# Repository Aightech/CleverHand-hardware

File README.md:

# CleverHand — Hardware

This repository contains the **hardware implementation** of the CleverHand platform.

CleverHand is an open-source, modular **Human–Machine Interface (HMI) platform** designed for
research, education, and rapid prototyping in neurotechnology, robotics, and human–robot interaction.

The hardware repository provides:

* modular PCB designs (KiCad),
* mechanical integration assets,
* manufacturing outputs,
* and per-module documentation and quality metadata.

> This repository focuses **only on hardware**.
> Firmware, software, tools, and platform-level documentation live in sibling repositories.

---

## Position in the CleverHand platform

CleverHand is structured as a **hardware / firmware / software stack**:

* **Hardware** (this repo)
  Modular, chainable PCBs for sensing, actuation, and interfacing with the human body.

* **Firmware**
  Low-level drivers, bus control, synchronization, and data transport.

* **Software & SDKs**
  Host interfaces (GUI, Python, C++, LSL, ROS, etc.).

This separation allows:

* independent evolution of hardware and software,
* reproducible research setups,
* and multiple integration paths (DIY, PCBA, pre-assembled).

---

## Intended use & scope

CleverHand hardware is designed for:

* research experiments,
* educational use,
* prototyping of assistive and interactive systems.

It is **not**:

* a medical device,
* a certified clinical system,
* a consumer product.

All designs are provided **as-is**, with readiness and quality explicitly documented per module.

---

## Design goals & constraints

| Constraint          | Status | Notes                        |
| ------------------- | :----: | ---------------------------- |
| Wearable            |   ⚒️   | Wireless support in progress |
| ≥16 channels        |    ✅   | Up to 256 channels (32 × 8)  |
| ≥2 kHz bandwidth    |    ✅   | Up to 2.5 kHz                |
| ≥16-bit resolution  |    ✅   | Up to 24-bit                 |
| Bipolar / monopolar |    ✅   | Module-dependent             |
| Modular             |    ✅   | 1–32 modules per bus         |
| Affordable          |    ✅   | ~£10–£30 per module          |
| Open-source         |    ✅   | Hardware, firmware, software |

---

## Hardware architecture overview

The hardware platform is built around a **chainable modular architecture**.

Each CleverHand system is composed of:

* a **controller** (host interface and timing),
* one **communication module** (bus arbitration),
* one or more **HMI modules**, assembled from submodules.

### Submodule types

HMI nodes are built by stacking standardized submodules:

* **Communication submodule**
  Address decoding, bus routing, chip-select handling.

* **Sensor submodule**
  Biosignal or motion acquisition (EMG, IMU, etc.).

* **Feedback submodule**
  User feedback (vibration, electrotactile stimulation, LEDs).

* **Interface submodule**
  Physical interface to the body (dry electrodes, jack, flex PCB).

This structure allows:

* rapid reconfiguration,
* high channel density,
* reuse of validated building blocks.

---

## Module catalog (hardware)

> The table below lists **implemented hardware designs**.
> Readiness (prototype / reference) and quality status are tracked via
> `description.yaml`, QC artifacts, and the generated catalog — not inferred from this table.

| Module                  | Description                            | Image                                                                      | Documentation                                            |
| ----------------------- | -------------------------------------- | -------------------------------------------------------------------------- | -------------------------------------------------------- |
| Communication (COM_MOD) | Bus communication and address decoding |                     | [README](pcb/hmi/communication/COM_MOD/README.md)            |
| EMG ADS1293             | 5-channel EMG acquisition              |  | [README](pcb/hmi/submodule/sensor/EMG_DAQ_ADS1293/README.md) |
| EMG ADS1298             | 8-channel EMG acquisition              |  | [README](pcb/hmi/submodule/sensor/EMG_DAQ_ADS1298/README.md) |
| EMG INA331              | Single-channel EMG + IMU               |            | [README](pcb/hmi/submodule/sensor/EMG_INA331/README.md)      |
| FES AO4882              | Electrotactile stimulation             |          | [README](pcb/hmi/submodule/feedback/FES_AO4882/README.md)    |
| IMU ICM-20948           | 9-axis IMU                             |        | [README](pcb/hmi/submodule/sensor/IMU_ICM20948/README.md)    |
| Dry electrodes (16ch)   | Rigid dry electrode interface          |             | [README](pcb/hmi/interface/DRY_ELEC_16CH/README.md)          |

---

## Bus architecture

CleverHand uses a **shared bus architecture** combining:

* a 5-bit address bus,
* SPI for high-rate data transfer,
* I²C for identification and configuration.

Each communication module:

* monitors the address bus,
* activates the chip-select of the targeted submodule,
* routes SPI transactions accordingly.

The full line list, connector pinout, enumeration protocol and the planned v3
changes (separable bus board, per-node I²C bridge) are specified in
**[docs/bus/README.md](docs/bus/README.md)**; the 3×10 soldered stack field that
links bus board, controller/communication module and submodules inside a node is
in **[docs/bus/interfaces.md](docs/bus/interfaces.md)**.

---

## Addressing & initialization

Module addressing is determined during an initialization phase based on
**physical position in the chain**.

Modules carry no hard-coded identity: the *n*-th node in the chain receives
address *n*, so identical modules can be placed anywhere.

Current status:

* deterministic, position-based addressing: **implemented** ([protocol](docs/bus/README.md#4-enumeration-position-based-addressing))
* re-enumeration without power cycle: **planned** (v3)
* dynamic hot-plugging: **not supported**

---

## Evaluation, QC & readiness

Hardware quality and maturity are **explicitly tracked**, not implied.

For each module:

* readiness level is declared in `description.yaml`,
* QC profiles and reports live in the module’s `qc/` folder,
* catalog readiness is generated automatically.

Only **REFERENCE-level modules** are considered stable and suitable
for external reuse without direct support.

---

## Repository structure

This repository contains the hardware designs and supporting assets for the CleverHand platform.

```
├── docs
│   ├── bus             # bus & protocol specification
│   ├── datasheet
│   ├── img
│   ├── initialisation
│   └── plots
├── LICENSE
├── pcb
│   ├── config_file
│   ├── controller
│   ├── hmi
│   └── tool
├── README.md
└── scripts
```

Each top-level directory has a clear, non-overlapping responsibility, described below.

---

## Relation to other repositories

* Firmware: see top-level CleverHand firmware repository
* Software / SDKs: see CleverHand interface repository
* Platform roadmap and policies: see top-level CleverHand README

---

## Status

The CleverHand hardware platform is **actively evolving**.

Some modules are experimental; others are approaching reference quality.
Authoritative status is always given by:

* module metadata,
* QC artifacts,
* and the generated catalog.

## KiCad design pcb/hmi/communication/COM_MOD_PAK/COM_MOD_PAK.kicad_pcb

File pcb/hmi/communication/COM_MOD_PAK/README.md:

# COM_MOD_PAK — v3 communication module, version B (HC32L110 + SLG46826)

> **Status:** KiCad project created with a generated draft schematic (all parts placed with values and nets attached by labels, no wiring tidy-up, empty PCB). Generator: `scripts/boards.py`. Plots below appear after running the jobset.

Master of a chain node. Keeps the HC32L110 and its v2 enumeration firmware;
the 74HC688 comparator is replaced by an SLG46826 GreenPAK whose LUTs are
written at runtime over a **private** 2-wire link from two of the freed GPIOs.
Carries the 3×10 stack field (see
[`docs/bus/interfaces.md`](../../../../docs/bus/interfaces.md)).

## Function

```mermaid
flowchart LR
    A[A0…A4] --> PAK[SLG46826\nLUT compare, async] --> CSB
    STOPI[STOP_IN] --> FW[HC32L110\ncount / latch n] --> STOPO[STOP_OUT]
    FW -->|private I²C: LUT config| PAK
    FW -->|client 0x08+n| I2C[hardware I²C client]
    SDA[SDA / SCL] --- I2C
    SDA --> BR[PCA9306\nEN = ¬CSB] --> SDAL[SDA_L / SCL_L]
    CSB --> INV[74LVC1G04] --> BR
```

- **Enumeration**: v2 firmware untouched except `set_address()`, which writes
  the PAK LUTs instead of five GPIOs. Pin map: SDA P35, SCL P36, STOP_IN P31,
  STOP_OUT P02, LED P01, PAK link P34/P33, AUX4 P03, AUX5 P15, AUX6 P14,
  AUX7 P32, user button P23, SWDIO P27, reset P00.
- **Decode**: 4-bit LUT one-hot on `A0…A3`, 2-bit LUT on `A4`, 3-bit LUT AND +
  invert. Blank / pre-init pattern decodes "never match". No oscillator, no
  DFF; quiescent < 1 µA.
- **Private link**: bit-banged I²C on two GPIOs to the PAK only, so the shared
  bus never sees the PAK and every PAK keeps its factory address.
- **I²C bridge, STOP, LED, re-enumeration**: as `COM_MOD_PIC`.

## Stack field (3×10, all PTH)

Same pin usage as `COM_MOD_PIC`; `AUX4`…`AUX7` on HC32L110 GPIOs P03/P15/P14/P32.

## Key parts

| Function | Part | Package |
| --- | --- | --- |
| MCU | HC32L110C6UA (as `COM_MOD`; the CSP-16 variant is not routable with JLC rules) | QFN-20 3×3 0.4 mm |
| Address decoder | SLG46826V | STQFN-20 2×3 0.4 mm |
| I²C bridge | PCA9306DQER | X2SON-8 1.4×0.8 |
| CSB inverter | SN74LVC1G04DPWR | X2SON-4 0.8×0.8 |
| LED | WS2812C-2020-V1 | 2.0×2.0 |
| Button | TS-1088R-02026 | SMD |
| Programming | SWD: SWDIO, SWCLK, reset pads | — |

Decoupling 100 nF + 1 µF 0402 per IC; pull-ups as for version A; 4.7 kΩ on the
private link.

## Bench before layout

- Decode propagation at 3.3 V on a GreenPAK dev board.
- LCSC / JLC stock of SLG46826V before committing to assembly.

## Electrical schematic

## PCB layout
| top | bottom |
| --- | --- |
|  |  |

## 3D model
[COM_MOD_PAK_3D](plots/COM_MOD_PAK_pcb.stl)

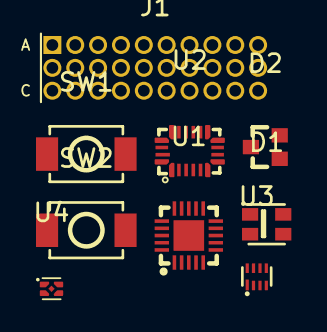
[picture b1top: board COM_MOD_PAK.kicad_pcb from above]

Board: 4 copper layers, 9 parts (0 on the bottom side), 25 nets, no tracks yet.

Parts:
D1: WS2812C-2020-V1; LED-SMD_4P-L2.0-W2.0-TL_WS2812B-2020
D2: BAT54SWT1G; SOT-323_L2.0-W1.3-P1.30-LS2.1-BR
J1: STACK 3x10; CLVHD_STACK_3x10
SW1, SW2: TS-1088R-02026; SW-SMD_L3.9-W3.0-P4.45
U1: HC32L110C6UA-SFN20TR; WQFN-20_L3.0-W3.0-P0.40-BL-EP
U2: SLG46826V_C5334557; STQFN-20_L3.0-W2.0-P0.40-BL
U3: PCA9306DQER; X2SON-8_L1.4-W1.0-P0.35-BL
U4: SN74LVC1G04DPWR; X2SON-4_L0.8-W0.8-P0.48-TL-A-1

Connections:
+3.3V: D1.4 (VDD), J1.4 (A2_3V3), U1.6 (VDD), U2.1 (VDD), U2.14 (VDD2), U3.2 (VREF1), U4.5 (VCC)
/BR_EN: U3.8 (EN), U4.4 (Y)
/BTN: SW2.1, U1.10 (LVDIN2/VCIN0/P23)
/LED_DI: D1.3 (DI), U1.2 (XTHI/AIN7/VCIN7/P01)
/PAK_SCL: U1.18 (P34/AIN4/VCIN4), U2.8 (SCL)
/PAK_SDA: U1.17 (P33/AIN3/VCIN3), U2.9 (SDA)
/RESETB: SW1.1, U1.1 (RESETB/P00)
A0: J1.2 (B1_A0), U2.2 (IO0)
A1: J1.5 (B2_A1), U2.3 (IO1)
A2: J1.8 (B3_A2), U2.4 (IO2)
A3: J1.11 (B4_A3), U2.5 (IO3)
A4: J1.14 (B5_A4), U2.6 (IO4)
AUX0: D2.1 (A), J1.9 (C3_AUX0)
AUX4: D2.3 (C/A), J1.21 (C7_AUX4), U1.7 (LVDIN1/P03)
AUX5: J1.24 (C8_AUX5), U1.8 (XTLO/P15)
AUX6: J1.27 (C9_AUX6), U1.9 (XTLI/P14)
AUX7: J1.30 (C10_AUX7), U1.16 (P32/AIN2/VCIN2)
CSB: J1.22 (A8_CSB), U2.7 (IO5), U4.2 (A)
GND: D1.2 (GND), J1.1 (A1_GND), J1.7 (A3_GND), J1.29 (B10_GND), SW1.2, SW2.2, U1.4 (VSS), U1.21 (PAD), U2.11 (GND), U3.1 (GND), U4.3 (GND)
SCL: J1.20 (B7_SCL), U1.20 (P36/AIN6/VCIN6/AVREF), U3.3 (SCL1)
SCL_L: J1.6 (C2_SCL_L), U3.6 (SCL2)
SDA: J1.17 (B6_SDA), U1.19 (P35/AIN5/VCIN5), U3.4 (SDA1)
SDA_L: J1.3 (C1_SDA_L), U3.5 (SDA2)
STOP_IN: J1.23 (B8_STOP_IN), U1.15 (P31/SWCLK)
STOP_OUT: J1.26 (B9_STOP_OUT), U1.3 (XTHO/AIN8/P02)

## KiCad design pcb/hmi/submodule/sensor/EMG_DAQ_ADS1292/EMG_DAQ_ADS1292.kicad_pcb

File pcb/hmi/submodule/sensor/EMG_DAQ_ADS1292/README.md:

# EMG ADS1292 Module
This module is a data acquisition module that embeds the ADS1292 analog front-end. It is responsible for acquiring the EMG signals from the electrodes.

## Electrical Schematic

## PCB Layout
|top view|side view|
|---|---|
 |  |  |

## 3D Model
[EMG_DAQ_ADS1292_3D](plots/EMG_DAQ_ADS1292_pcb.stl)

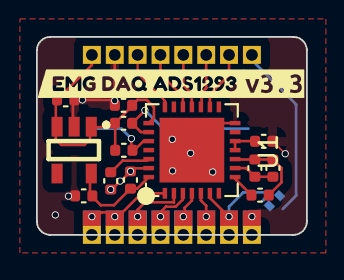
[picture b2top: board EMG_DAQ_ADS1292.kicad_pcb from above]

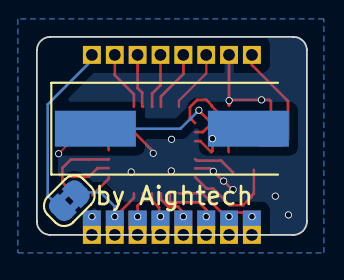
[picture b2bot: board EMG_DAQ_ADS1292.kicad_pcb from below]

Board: 4 copper layers, 15.0 x 11.0 mm, 33 parts (2 on the bottom side), 22 nets.

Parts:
C1, C5, C7: 100nF; C_0402_1005Metric
C2, C8, C9: 1uF; C_0402_1005Metric
C3, C4: 22pF; C_0402_1005Metric
C6: 1nF; C_0402_1005Metric
J1, J2, J3, J4, J5, J6, J7, J8, J9, J10, J11, J12, J13, J14, J15, J16: Conn_01x01_Pin; PinHeader_1x01_P1.27mm_Vertical
JP2: SolderJumper_2_Bridged; SolderJumper-2_P1.3mm_Bridged2Bar_RoundedPad1.0x1.5mm
R1: 10K; C_0402_1005Metric
R2: 10M; C_0402_1005Metric
U1: ADS1293CISQE-NOPB; ADS1293CISQE
U2: AP2112K-3.3TRG1; SOT-25-5_L2.9-W1.6-P0.95-LS2.8-BL
Y1: Crystal; Crystal_SMD_HC49-SD
kibuzzard-658D7E24: G***; kibuzzard-658D7E24
kibuzzard-69472C09: G***; kibuzzard-69472C09

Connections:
+3.3V: C3.1, C4.1, C5.1, C9.1, J13.1, U1.22 (VDDIO), U2.1 (VIN), U2.3 (EN)
+3.3VA: C1.1, C8.1, U1.28 (VDD), U2.5 (VOUT)
/CLK: J1.1, U1.21 (CLK)
/CMOUT: R1.2, U1.8 (CMOUT)
/CSB: J12.1, U1.16 (CSB)
/PICO: J10.1, U1.18 (SDI)
/POCI: J9.1, U1.19 (SDO)
/RLDINV: C6.1, R1.1, R2.1, U1.10 (RLDINV)
/RLDOUT: C6.2, R2.2, U1.9 (RLDOUT)
/RLDREF: C7.1, U1.11 (RLDIN), U1.12 (RLDREF)
/SCLK: J11.1, U1.17 (SCLK)
/cvref: C2.1, U1.26 (CVREF)
/extRef: J7.1, JP2.1 (A)
/in1: J2.1, J3.1, U1.1 (IN1)
/in2: J4.1, U1.2 (IN2)
/in3: J5.1, U1.3 (IN3)
/in4: J6.1, U1.4 (IN4)
/in5: J8.1, U1.5 (IN5)
/in6: J15.1, JP2.2 (B), U1.6 (IN6)
GND: C1.2, C2.2, C5.2, C7.2, C8.2, C9.2, J14.1, J16.1, U1.14 (VSSIO), U1.27 (VSS), U1.29 (EPAD), U2.2 (GND)
XTAL1: C4.2, U1.23 (XTAL1), Y1.1
XTAL2: C3.2, U1.24 (XTAL2), Y1.2

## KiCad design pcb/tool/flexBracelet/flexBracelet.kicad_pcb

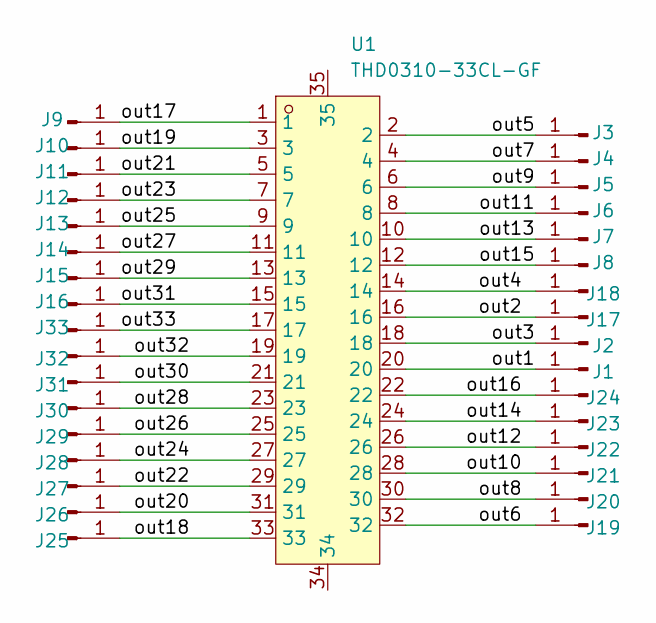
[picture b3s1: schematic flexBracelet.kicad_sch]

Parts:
J1, J2, J3, J4, J5, J6, J7, J8, J9, J10, J11, J12, J13, J14, J15, J16, J17, J18, J19, J20, J21, J22, J23, J24, J25, J26, J27, J28, J29, J30, J31, J32, J33: Conn_01x01_Pin; dryElec8x4mm
U1: THD0310-33CL-GF; FPC 33POS 0.3MM; LCSC Part C19078615

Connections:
/out1: J1.1 (Pin_1_1), U1.20 (20_20)
/out2: J17.1 (Pin_1_1), U1.16 (16_16)
/out3: J2.1 (Pin_1_1), U1.18 (18_18)
/out4: J18.1 (Pin_1_1), U1.14 (14_14)
/out5: J3.1 (Pin_1_1), U1.2 (2_2)
/out6: J19.1 (Pin_1_1), U1.32 (32_32)
/out7: J4.1 (Pin_1_1), U1.4 (4_4)
/out8: J20.1 (Pin_1_1), U1.30 (30_30)
/out9: J5.1 (Pin_1_1), U1.6 (6_6)
/out10: J21.1 (Pin_1_1), U1.28 (28_28)
/out11: J6.1 (Pin_1_1), U1.8 (8_8)
/out12: J22.1 (Pin_1_1), U1.26 (26_26)
/out13: J7.1 (Pin_1_1), U1.10 (10_10)
/out14: J23.1 (Pin_1_1), U1.24 (24_24)
/out15: J8.1 (Pin_1_1), U1.12 (12_12)
/out16: J24.1 (Pin_1_1), U1.22 (22_22)
/out17: J9.1 (Pin_1_1), U1.1 (1_1)
/out18: J25.1 (Pin_1_1), U1.33, U1.34 (33_33)
/out19: J10.1 (Pin_1_1), U1.3 (3_3)
/out20: J26.1 (Pin_1_1), U1.31 (31_31)
/out21: J11.1 (Pin_1_1), U1.5 (5_5)
/out22: J27.1 (Pin_1_1), U1.29 (29_29)
/out23: J12.1 (Pin_1_1), U1.7 (7_7)
/out24: J28.1 (Pin_1_1), U1.27 (27_27)
/out25: J13.1 (Pin_1_1), U1.9 (9_9)
/out26: J29.1 (Pin_1_1), U1.25 (25_25)
/out27: J14.1 (Pin_1_1), U1.11 (11_11)
/out28: J30.1 (Pin_1_1), U1.23 (23_23)
/out29: J15.1 (Pin_1_1), U1.13 (13_13)
/out30: J31.1 (Pin_1_1), U1.21 (21_21)
/out31: J16.1 (Pin_1_1), U1.15 (15_15)
/out32: J32.1 (Pin_1_1), U1.19 (19_19)
/out33: J33.1 (Pin_1_1), U1.17 (17_17)

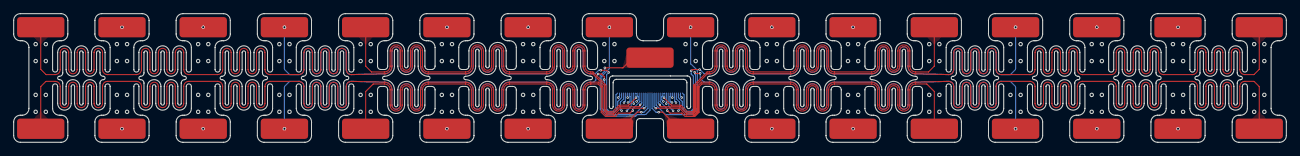
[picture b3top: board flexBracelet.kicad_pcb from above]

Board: 4 copper layers, 188.0 x 19.0 mm, 34 parts (1 on the bottom side), 33 nets.

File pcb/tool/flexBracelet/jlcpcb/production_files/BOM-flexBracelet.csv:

Comment,Designator,Footprint,LCSC,Quantity
THD0310-33CL-GF,U1,FPC 33POS 0.3MM,C19078615,1
Conn_01x01_Pin,J33,dryElec8x4mm,,1
Conn_01x01_Pin,J29,dryElec8x4mm,,1
Conn_01x01_Pin,J24,dryElec8x4mm,,1
Conn_01x01_Pin,J5,dryElec8x4mm,,1
Conn_01x01_Pin,J28,dryElec8x4mm,,1
Conn_01x01_Pin,J20,dryElec8x4mm,,1
Conn_01x01_Pin,J6,dryElec8x4mm,,1
Conn_01x01_Pin,J25,dryElec8x4mm,,1
Conn_01x01_Pin,J21,dryElec8x4mm,,1
Conn_01x01_Pin,J10,dryElec8x4mm,,1
Conn_01x01_Pin,J23,dryElec8x4mm,,1
Conn_01x01_Pin,J30,dryElec8x4mm,,1
Conn_01x01_Pin,J11,dryElec8x4mm,,1
Conn_01x01_Pin,J31,dryElec8x4mm,,1
Conn_01x01_Pin,J14,dryElec8x4mm,,1
Conn_01x01_Pin,J13,dryElec8x4mm,,1
Conn_01x01_Pin,J32,dryElec8x4mm,,1
Conn_01x01_Pin,J4,dryElec8x4mm,,1
Conn_01x01_Pin,J3,dryElec8x4mm,,1
Conn_01x01_Pin,J16,dryElec8x4mm,,1
Conn_01x01_Pin,J18,dryElec8x4mm,,1
Conn_01x01_Pin,J9,dryElec8x4mm,,1
Conn_01x01_Pin,J17,dryElec8x4mm,,1
Conn_01x01_Pin,J12,dryElec8x4mm,,1
Conn_01x01_Pin,J27,dryElec8x4mm,,1
Conn_01x01_Pin,J19,dryElec8x4mm,,1
Conn_01x01_Pin,J2,dryElec8x4mm,,1
Conn_01x01_Pin,J15,dryElec8x4mm,,1
Conn_01x01_Pin,J22,dryElec8x4mm,,1
Conn_01x01_Pin,J1,dryElec8x4mm,,1
Conn_01x01_Pin,J8,dryElec8x4mm,,1
Conn_01x01_Pin,J7,dryElec8x4mm,,1
Conn_01x01_Pin,J26,dryElec8x4mm,,1

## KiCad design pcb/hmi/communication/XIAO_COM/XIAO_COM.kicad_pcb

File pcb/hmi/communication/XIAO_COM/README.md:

# XIAO_COM — Seeed XIAO ESP32-S3 mono controller

`XIAO_COM` is a controller board in the **node form factor**: it sits directly on
top of a CleverHand submodule stack (like `MONO_CTRL`) instead of driving a chain
through the bus. It carries a Seeed XIAO ESP32-S3 module, a 6-axis IMU, a
battery fuel gauge and a status LED. It is the ESP32-S3 candidate of the
nRF52840-versus-ESP32-S3 evaluation (autonomy, link throughput, performance).

The XIAO module itself is bought separately from Seeed Studio and soldered on
the bottom side.

## Hardware

| Component | Part | Function | Interface to the XIAO |
| --- | --- | --- | --- |
| MCU module | XIAO ESP32-S3 | Dual-core ESP32-S3, Wi-Fi + BLE, USB-C, on-module LiPo charger | — |
| IMU | ICM-42670 (LGA-14) | 3-axis accelerometer + 3-axis gyroscope | SPI shared with the stack, `CS` = GPIO5, `INT1` = GPIO6, `FSYNC` = GPIO43 |
| Fuel gauge | BQ27421-G1A (DSBGA-9) | Battery state of charge, current sense | I²C `SDA` = GPIO2, `SCL` = GPIO3 |
| Status LED | WS2812B-2020 | Single NeoPixel | Data = GPIO1 |
| Stack header `J4` | 1×10, 1.27 mm | Submodule interface (see below) | |
| Battery `J1` / `J2` | 2× 1×2, 1.27 mm | Battery in (through the gauge sense path) / battery out | |
| Jumper `JP1` | 3-pad solder jumper | Routes the battery through the fuel-gauge sense input (`SRX`, default, pads 1-2) or bypasses it (pads 2-3) | |

Board size ≈ 18 × 20 mm, 2 layers, components on both sides.

## Stack header `J4` (submodule interface)

`J4` reproduces the "bus row" of the v2 submodule stack, so the board drops onto
any `EMG_DAQ_*` / `IMU_*` submodule without a communication module.

| Pin | Signal | XIAO GPIO | Notes |
| --: | --- | --- | --- |
| 1 | `AUX1` | — | pass-through pad only |
| 2 | `3V3` | `3V3` | from the XIAO regulator |
| 3 | `GND` | `GND` | |
| 4 | `AUX3` | — | pass-through pad only |
| 5 | `POCI` | GPIO8 (MISO) | shared with the IMU `SDO` |
| 6 | `PICO` | GPIO9 (MOSI) | shared with the IMU `SDI` |
| 7 | `SCLK` | GPIO7 (SCK) | shared with the IMU `SCLK` |
| 8 | `CSB` | GPIO44 | chip-select of the submodule, active low |
| 9 | `AREF` (`extRef`) | — | pass-through pad only, no DAC on this board |
| 10 | `AUX2` | GPIO4 | spare GPIO / ADC input |

Not present on the header: the shared I²C (`SDA`/`SCL` only reach the fuel
gauge) and the ARM/SWD row. I²C-only submodules (e.g. a `DRV2625` haptic
driver) are therefore **not** reachable from this revision; the v3 stack
interface adds the local I²C segment (see [`docs/bus`](../../../../docs/bus/README.md)).

## Power

- Battery on `J1` (+, GND) is measured by the BQ27421 and delivered on `+BATT`
  (`J2`). Charging and the 3.3 V rail come from the XIAO module.
- `JP1` lets you bypass the gauge sense path for tests without the gauge.

## Bus role

Mono controller only: no bus connector, no address lines, no enumeration.
`CSB` is driven directly by GPIO44. To head a chain, use a shield
(`S_XIAO`) or the planned separable bus board.

## Electrical schematic
[XIAO_COM.pdf](plots/XIAO_COM.pdf) (schematic PDF)

## PCB layout
| top | bottom |
| --- | --- |
|  |  |

## 3D model
[XIAO_COM.step](plots/XIAO_COM.step) · [XIAO_COM.stl](plots/XIAO_COM.stl)

## Notes
- Plot files still carry the pre-refactor name `XIAO_ADAPTER`; regenerate with the jobset to rename them.
- The schematic title block still reads "EMG ADS1298" (copied template); update on next edit.

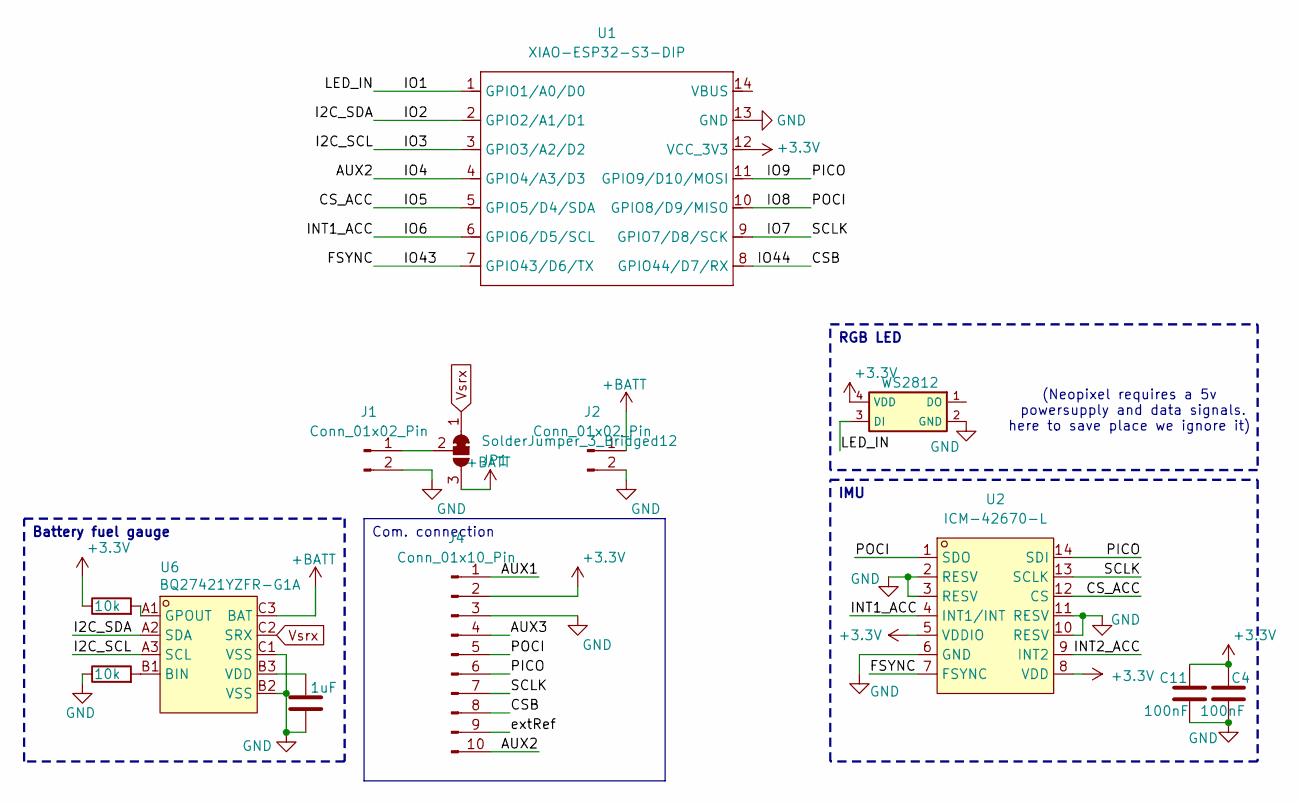
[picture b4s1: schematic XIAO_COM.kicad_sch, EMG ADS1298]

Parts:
C4, C11: 100nF; C_0402_1005Metric; LCSC C1525
C28: 1uF; C_0201_0603Metric; LCSC C52923
J1, J2: Conn_01x02_Pin; PinHeader_1x02_P1.27mm_Vertical
J4: Conn_01x10_Pin; PinHeader_1x10_P1.27mm_Vertical
JP1: SolderJumper_3_Bridged12; SolderJumper-3_P1.3mm_Bridged12_RoundedPad1.0x1.5mm_NumberL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
R10, R17: 10k; R_0201_0603Metric; LCSC C25744
U1: XIAO-ESP32-S3-DIP; XIAO-ESP32S3-DIP
U2: ICM-42670-L; LGA-14_L3.0-W2.5-P0.50-TL_QMI8658A; LCSC Part C49073546
U6: BQ27421YZFR-G1A; DSBGA-9_L1.5-W1.5-R3-C3-P0.50-BL; LCSC Part C139621
U10: WS2812; LED-SMD_4P-L2.0-W2.0-TL_WS2812B-2020; LCSC C2976072

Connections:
+3.3V: C4.1, C11.1, J4.2, R17.1, U1.12 (VCC_3V3), U2.5 (VDDIO), U2.8 (VDD), U10.4 (VDD)
+BATT: J2.1, JP1.3 (B), U6.C3 (BAT)
/AUX1: J4.1
/AUX2: J4.10, U1.4 (GPIO4/A3/D3)
/AUX3: J4.4
/CSB: J4.8, U1.8 (GPIO44/D7/RX)
/CS_ACC: U1.5 (GPIO5/D4/SDA), U2.12 (CS)
/FSYNC: U1.7 (GPIO43/D6/TX), U2.7 (FSYNC)
/I2C_SCL: U1.3 (GPIO3/A2/D2), U6.A3 (SCL)
/I2C_SDA: U1.2 (GPIO2/A1/D1), U6.A2 (SDA)
/INT1_ACC: U1.6 (GPIO6/D5/SCL), U2.4 (INT1/INT)
/INT2_ACC: U2.9 (INT2)
/IO1: U1.1 (GPIO1/A0/D0), U10.3 (DI)
/IO7: J4.7, U1.9 (GPIO7/D8/SCK), U2.13 (SCLK)
/IO8: J4.5, U1.10 (GPIO8/D9/MISO), U2.1 (SDO)
/IO9: J4.6, U1.11 (GPIO9/D10/MOSI), U2.14 (SDI)
/extRef: J4.9
GND: C4.2, C11.2, C28.2, J1.2, J2.2, J4.3, R10.1, U1.13 (GND), U2.2 (RESV), U2.3 (RESV), U2.6 (GND), U2.10 (RESV), U2.11 (RESV), U6.B2 (VSS), U6.C1 (VSS), U10.2 (GND)
unnamed: J1.1, JP1.2 (C)
unnamed: R10.2, U6.B1 (BIN)
unnamed: R17.2, U6.A1 (GPOUT)
unnamed: C28.1, U6.B3 (VDD)
Vsrx: JP1.1 (A), U6.C2 (SRX)

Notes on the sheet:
(Neopixel requires a 5v powersupply and data signals. here to save place we ignore it)
RGB LED
IMU
Battery fuel gauge
Com. connection

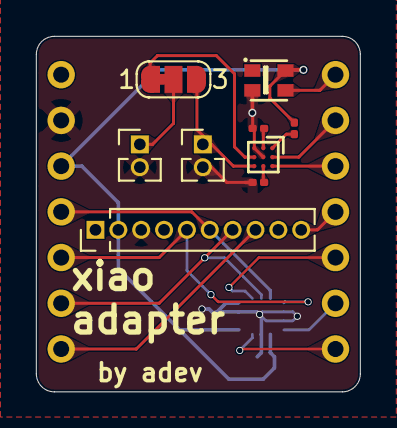
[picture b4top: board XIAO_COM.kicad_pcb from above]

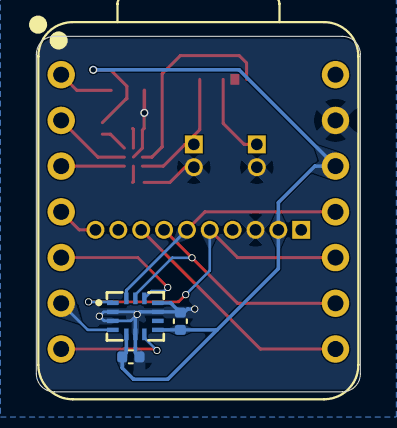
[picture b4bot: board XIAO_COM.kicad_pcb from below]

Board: 2 copper layers, 18.0 x 19.8 mm, 13 parts (4 on the bottom side), 19 nets.

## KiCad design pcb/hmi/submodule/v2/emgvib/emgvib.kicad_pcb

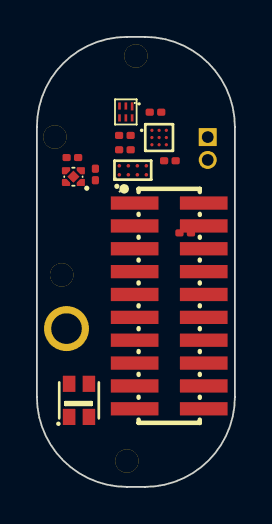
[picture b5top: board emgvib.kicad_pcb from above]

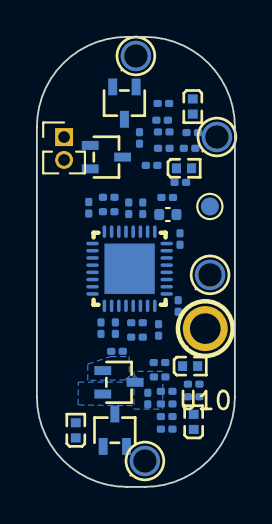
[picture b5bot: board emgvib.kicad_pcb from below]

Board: 4 copper layers, 11.0 x 25.0 mm, 63 parts (50 on the bottom side), 35 nets, no tracks yet.

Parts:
C57, C58, C60, C61, C62, C119, C120, C123, C124, C126, C130, C131: 4.7nF; C_0201_0603Metric
C59: 1.5nF; C_0201_0603Metric
C66, C69, C71, C72, C133, C135: 1uF; C_0201_0603Metric
C127: 10uF; C_0402_1005Metric
C128, C129: 100nF; C_0201_0603Metric
D18, D19, D20, D41, D42: PGB1010402KR; D0402
D21, D22, D45, D46: BAT54SWFILM; SOT-323-3_L2.0-W1.3-P1.30-LS2.1-BR
J7: Conn_01x02_Pin; PinHeader_1x02_P1.27mm_Vertical
R48, R49, R52, R53, R63, R64, R97, R98, R101, R102, R103, R104, R105, R106: 10K; R_0201_0603Metric
R50, R54: 100k; R_0201_0603Metric
R51: 1M; R_0201_0603Metric
R55: 0R; R_0201_0603Metric
TP_VDD_6: TestPoint; TestPoint_Pad_D1.0mm
U1: PZ127-2-10-S; HDR-SMD_PZ127-2-10-S
U2: PCA9306YZTR; DSBGA-8_L1.9-W0.9-R2-C4-P0.50-BL
U3: SN74LVC1G04DSFR; UDFN-6_L1.0-W1.0-P0.35-BL
U5, U6, U8, U9: YZP0120-16020-01; SMD_YZP0120-16020-01
U7: WS2812-2020; LED-SMD_4P-L2.0-W2.0-TL_WS2812B-2020
U10: YZP0664-20036-01; CONN-TH_YZP0664-20036-01
U12: ADS1292RIRSMR; QFN-32_L4.0-W4.0-P0.40-TL-EP2.8
U23: TPS7A0230PDQNR; UDFN-4_L1.0-W1.0-P0.65-TL
U27: DRV2625YFFR; DSBGA-9_L1.4-W1.3-R3-C3-P0.40-BL

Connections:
/CS: R106.1, U3.2 (A), U12.18 (~CS)
/ELEC_N1: D19.2, R49.2, U5.1 (1_1)
/ELEC_N2: D42.2, R98.2, U8.1 (1_1)
/ELEC_P1: D18.2, R48.2, U10.1 (1_1)
/ELEC_P2: D41.2, R97.2, U6.1 (1_1)
/IN_N1: C61.1, C62.2, D22.3, R53.1, U12.3 (IN1N)
/IN_N2: C124.1, C126.2, D46.3, R102.1, U12.5 (IN2N)
/IN_P1: C60.1, C62.1, D21.3, R52.1, U12.4 (IN1P)
/IN_P2: C123.1, C126.1, D45.3, R101.1, U12.6 (IN2P)
/OUTN: J7.2, U27.C3 (OUT-)
/OUTP: J7.1, U27.A3 (OUT+)
/RLD_IN: R54.2, R55.1, U12.29 (RLDIN/RLDREF)
/RLD_INV: C59.2, R51.1, U12.28 (RLDINV)
/RLD_OUT: C59.1, R50.1, R51.2, R54.1, U12.30 (RLDOUT)
/SCL: R63.1, U2.C2 (SCL2), U27.C1 (SCL)
/SDA: R64.1, U2.D2 (SDA2), U27.B1 (SDA)
/VDDA: C69.2, C128.1, D21.2, D22.2, D45.2, D46.2, TP_VDD_6.1 (1_1), U12.12 (AVDD), U23.1 (OUT)
/VREFP: C127.1, C129.1, U12.9 (VREFP)
GND: C57.2, C58.2, C60.2, C61.2, C66.1, C69.1, C71.1, C72.1, C119.2, C120.2, C123.2, C124.2, C127.2, C128.2, C129.2, C133.1, C135.2, D18.1, D19.1, D20.2, D21.1, D22.1, D41.1, D42.1, D45.1, D46.1, R55.2, R103.1, U2.A1 (GND), U3.3 (GND), U7.2 (GND), U12.10 (VREFN), U12.13 (AVSS), U12.24 (DGND), U12.33 (EP), U23.2 (GND), U23.5 (EP), U27.A1 (TRIG/INTZ), U27.B3 (GND)
unnamed: C57.1, R48.1, R52.2
unnamed: C58.1, R49.1, R53.2
unnamed: C119.1, R97.1, R101.2
unnamed: C120.1, R98.1, R102.2
unnamed: D20.1, R50.2, U9.1 (1_1)
unnamed: U2.A2 (EN), U3.4 (Y)
unnamed: R103.2, R104.2, U12.14 (CLKSEL)
unnamed: C131.1, U12.1 (PGA1N)
unnamed: C131.2, U12.2 (PGA1P)
unnamed: C130.1, U12.7 (PGA2N)
unnamed: C130.2, U12.8 (PGA2P)
unnamed: C133.2, U12.11 (VCAP1)
unnamed: C135.1, U12.27 (VCAP2)
unnamed: R105.2, U12.15 (~PWDN/~RESET)
unnamed: C71.2, U27.A2 (REG)
VDDF: C66.2, C72.2, R63.2, R64.2, R104.1, R105.1, R106.2, U2.B1 (VREF1), U2.B2 (VREF2), U3.6 (VCC), U7.4 (VDD), U12.23 (DVDD), U23.3 (EN), U23.4 (IN), U27.B2 (NRST), U27.C2 (VDD)

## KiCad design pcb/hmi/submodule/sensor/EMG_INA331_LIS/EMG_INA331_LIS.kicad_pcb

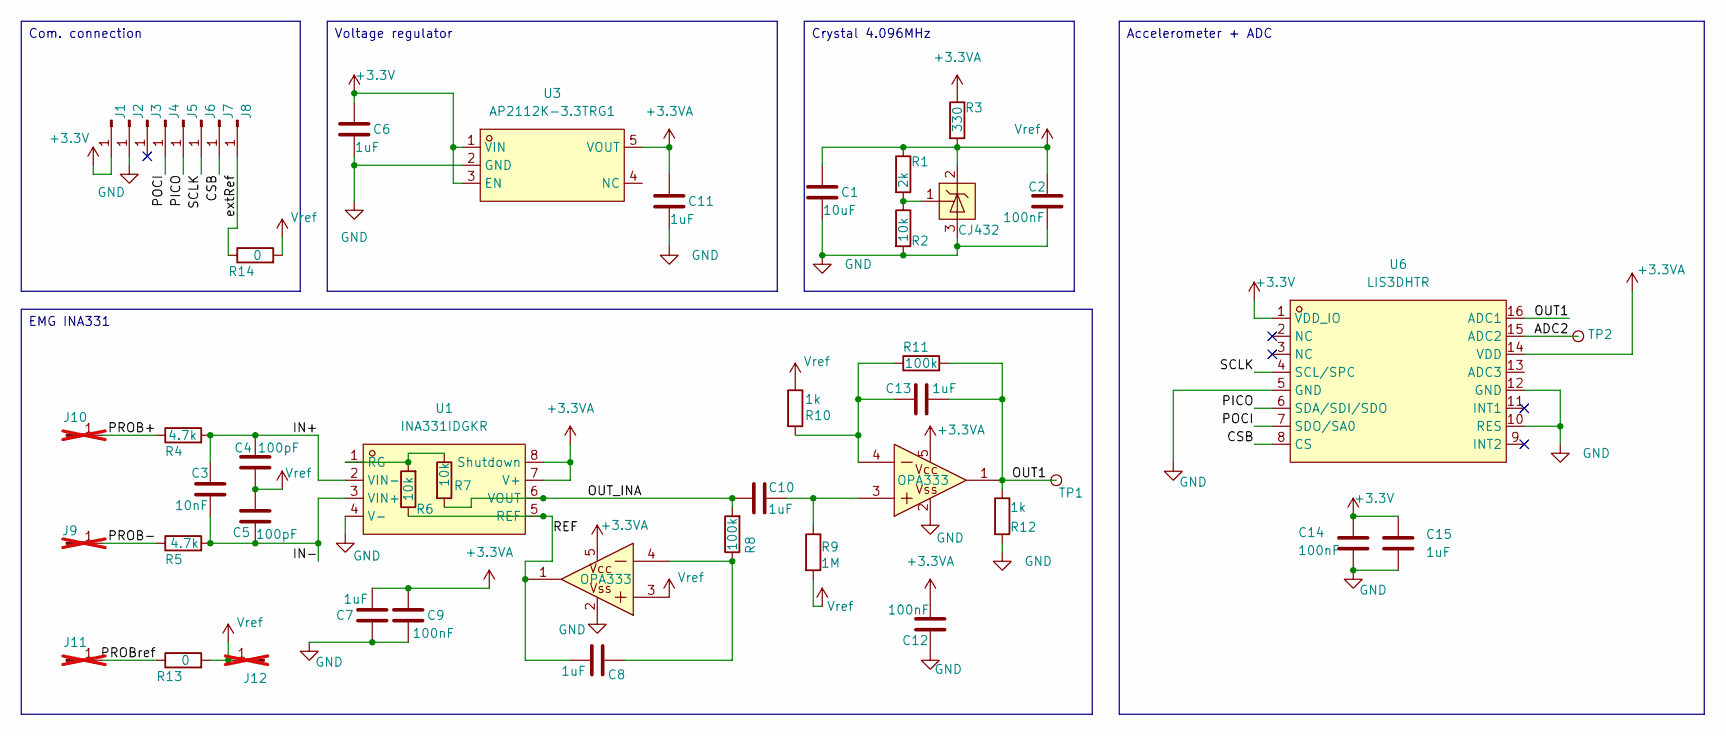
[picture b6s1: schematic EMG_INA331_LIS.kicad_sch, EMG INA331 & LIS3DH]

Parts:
C1: 10uF; C_0402_1005Metric
C2, C9, C12, C14: 100nF; C_0402_1005Metric
C3: 10nF; C_0402_1005Metric
C4, C5: 100pF; C_0402_1005Metric; LCSC C1546
C6, C7, C8, C10, C11, C13, C15: 1uF; C_0402_1005Metric
J1, J2, J3, J4, J5, J6, J7, J8: Conn_01x01_Pin; PinHeader_1x01_P1.27mm_Vertical
J9, J10, J11, J12: Conn_01x01_Pin; PinHeader_1x01_P1.27mm_Vertical; not fitted
R1: 2k; R_0402_1005Metric; LCSC C4109
R2: 10k; R_0402_1005Metric; LCSC C25744
R3: 330; R_0402_1005Metric; LCSC C25104
R4: 4.7k; R_0402_1005Metric; LCSC C25900
R5: 4.7k; R_0402_1005Metric
R6, R7: 10k; R_0402_1005Metric
R8: 100k; R_0402_1005Metric
R9: 1M; R_0402_1005Metric; LCSC C26083
R10: 1k; R_0402_1005Metric; LCSC C11702
R11: 100k; R_0402_1005Metric; LCSC C25741
R12: 1k; R_0402_1005Metric
R13, R14: 0; R_0402_1005Metric; LCSC C17168
TP1, TP2: TestPoint; TestPoint_Pad_D1.0mm
U1: INA331IDGKR; VSSOP-8_L3.0-W3.0-P0.65-LS5.0-BL; LCSC Part C2863664
U2, U4: OPA333; SOT-23-5_L2.9-W1.6-P0.95-LS2.8-BR; LCSC Part C3007938
U3: AP2112K-3.3TRG1; SOT-25-5_L2.9-W1.6-P0.95-LS2.8-BL; LCSC Part C51118
U5: CJ432; SOT-23-3_L2.9-W1.3-P1.90-LS2.4-BR; LCSC Part C2910208
U6: LIS3DHTR; LGA-16_L3.0-W3.0-P0.50-TL; LCSC Part C15134

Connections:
+3.3V: C6.1, C14.1, C15.1, J1.1 (Pin_1_1), U3.1 (VIN), U3.3 (EN), U6.1 (VDD_IO)
+3.3VA: C7.2, C9.1, C11.1, C12.1, R3.1, U1.7 (V+), U1.8 (Shutdown), U2.5 (V+), U3.5 (VOUT), U4.5 (V+), U6.14 (VDD)
/ADC2: TP2.1 (1_1), U6.15 (ADC2)
/CSB: J7.1 (Pin_1_1), U6.8 (CS)
/IN+: C3.1, C4.1, R4.2, U1.2 (VIN-)
/IN-: C3.2, C5.2, R5.2, U1.3 (VIN+)
/OUT1: C13.2, R11.2, R12.1, TP1.1 (1_1), U4.1 (OUT), U6.16 (ADC1)
/OUT_INA: C10.1, R7.2, R8.2, U1.6 (VOUT)
/PICO: J5.1 (Pin_1_1), U6.6 (SDA/SDI/SDO)
/POCI: J4.1 (Pin_1_1), U6.7 (SDO/SA0)
/PROB+: J10.1 (Pin_1_1), R4.1
/PROB-: J9.1 (Pin_1_1), R5.1
/PROBref: J11.1 (Pin_1_1), R13.1
/REF: C8.1, R6.1, U1.5 (REF), U2.1 (OUT)
/SCLK: J6.1 (Pin_1_1), U6.4 (SCL/SPC)
/extRef: J8.1 (Pin_1_1), R14.1
GND: C1.2, C2.2, C6.2, C7.1, C9.2, C11.2, C12.2, C14.2, C15.2, J2.1 (Pin_1_1), R2.2, R12.2, U1.4 (V-), U2.2 (V-), U3.2 (GND), U4.2 (V-), U5.3 (A), U6.5 (GND), U6.10 (RES), U6.12 (GND)
unnamed: R6.2, R7.1, U1.1 (RG)
unnamed: C8.2, R8.1, U2.4 (-IN)
unnamed: C10.2, R9.1, U4.3 (+IN)
unnamed: C13.1, R10.2, R11.1, U4.4 (-IN)
unnamed: R1.2, R2.1, U5.1 (R)
Vref: C1.1, C2.1, C4.2, C5.1, J12.1 (Pin_1_1), R1.1, R3.2, R9.2, R10.1, R13.2, R14.2, U2.3 (+IN), U5.2 (K)

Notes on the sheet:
Com. connection
Crystal 4.096MHz
Accelerometer + ADC
Voltage regulator
EMG INA331

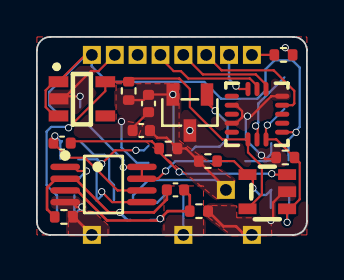
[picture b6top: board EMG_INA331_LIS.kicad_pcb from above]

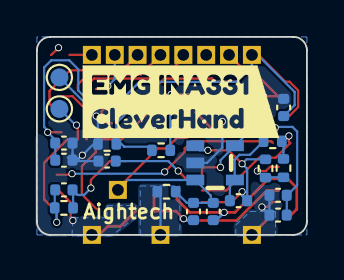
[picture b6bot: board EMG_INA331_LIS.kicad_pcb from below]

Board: 4 copper layers, 15.0 x 11.0 mm, 50 parts (22 on the bottom side), 23 nets.

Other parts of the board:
kibuzzard-6606B2BA: G***; kibuzzard-6606B2BA

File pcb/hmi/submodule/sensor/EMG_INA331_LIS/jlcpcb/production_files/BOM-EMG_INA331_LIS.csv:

Comment,Designator,Footprint,LCSC,Quantity
0,"R13,R14",R_0402_1005Metric,C17168,2
100k,"R11,R8",R_0402_1005Metric,C25741,2
100nF,"C12,C14,C2,C9",C_0402_1005Metric,C1525,4
100pF,"C4,C5",C_0402_1005Metric,C1546,2
10k,"R2,R6,R7",R_0402_1005Metric,C25744,3
10nF,C3,C_0402_1005Metric,C15195,1
10uF,C1,C_0402_1005Metric,C15525,1
1M,R9,R_0402_1005Metric,C26083,1
1k,"R10,R12",R_0402_1005Metric,C11702,2
1uF,"C10,C11,C13,C15,C6,C7,C8",C_0402_1005Metric,C52923,7
2k,R1,R_0402_1005Metric,C4109,1
330,R3,R_0402_1005Metric,C25104,1
4.7k,"R4,R5",R_0402_1005Metric,C25900,2
AP2112K-3.3TRG1,U3,SOT-25-5_L2.9-W1.6-P0.95-LS2.8-BL,C51118,1
CJ432,U5,SOT-23-3_L2.9-W1.3-P1.90-LS2.4-BR,C2910208,1
INA331IDGKR,U1,VSSOP-8_L3.0-W3.0-P0.65-LS5.0-BL,C2863664,1
LIS3DHTR,U6,LGA-16_L3.0-W3.0-P0.50-TL,C15134,1
OPA333,"U2,U4",SOT-23-5_L2.9-W1.6-P0.95-LS2.8-BR,C3007938,2

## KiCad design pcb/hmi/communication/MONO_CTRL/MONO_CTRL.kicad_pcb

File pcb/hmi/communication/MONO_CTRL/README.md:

# Standalone mono-module controller
 This module is a standalone controller node that can be used to control a single submodule. It enanble standalone hmi module without the need for a cleverhand bus.

## Electrical Schematic

## PCB Layout
|top view|side view|
|---|---|
 |  |  |

## 3D Model
[MONO_CTRL_3D](plots/MONO_CTRL_pcb.stl)

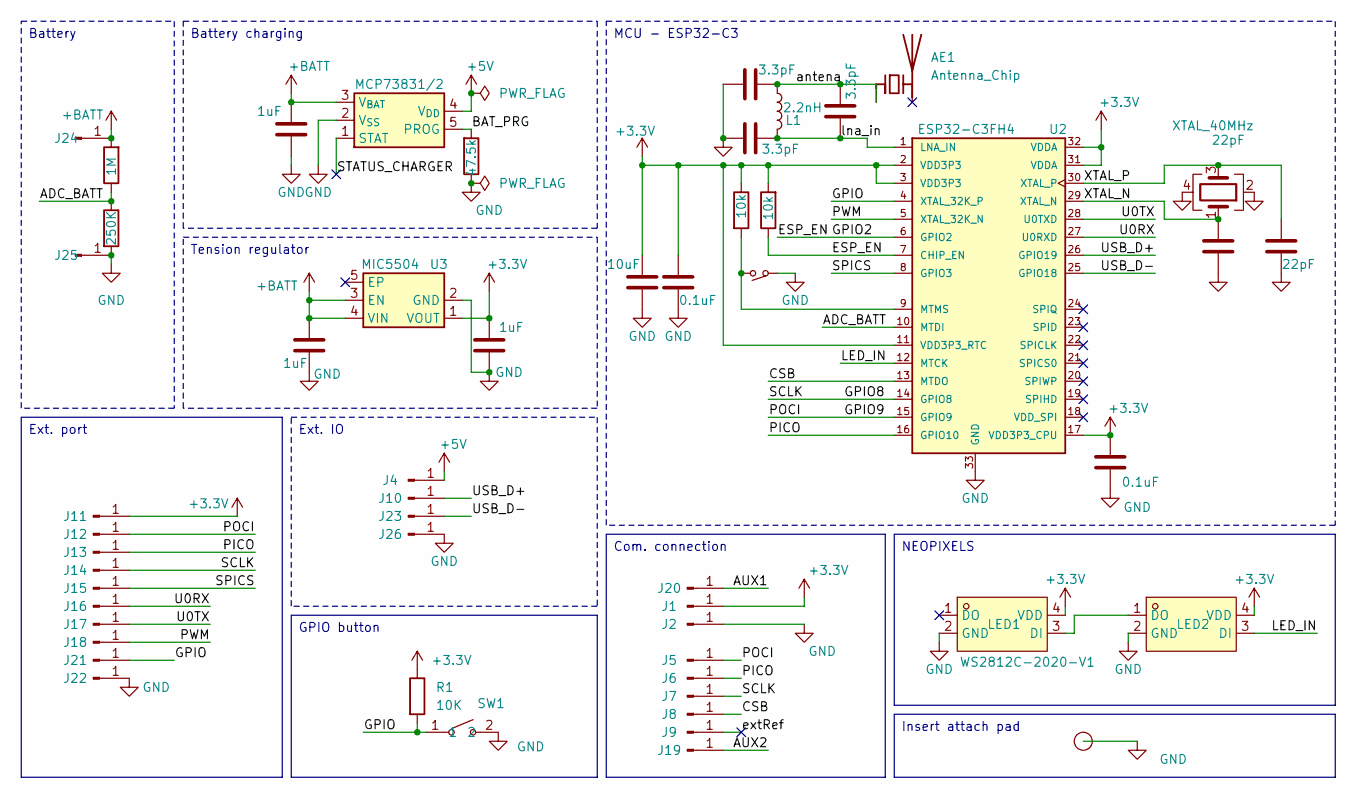
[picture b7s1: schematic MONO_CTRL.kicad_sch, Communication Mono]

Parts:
AE1: Antenna_Chip; C_1206_3216Metric; LCSC C6807751
C1, C3, C12: 3.3pF; C_0402_1005Metric
C2, C8, C9: 1uF; C_0402_1005Metric
C4: 22pF; C_0402_1005Metric; LCSC C12530
C5: 22pF; C_0402_1005Metric; LCSC C1532
C6: 10uF; C_0402_1005Metric
C7, C10: 0.1uF; C_0402_1005Metric
I1: smd_insert; insert_1.2mm
J1, J2, J4, J5, J6, J7, J8, J9, J10, J11, J12, J13, J14, J15, J16, J17, J18, J19, J20, J21, J22, J23, J24, J25, J26: Conn_01x01_Pin; PinHeader_1x01_P1.27mm_Vertical
L1: 2.2nH; L_0402_1005Metric
LED1: WS2812C-2020-V1; LED-SMD_4P-L2.0-W2.0-TL_WS2812B-2020; LCSC Part C2976072
LED2: WS2812C; LED-SMD_4P-L2.0-W2.0-TL_WS2812B-2020; LCSC Part C2976072
R1: 10K; R_0402_1005Metric; LCSC C25744
R2: 47.5k; R_0402_1005Metric; LCSC C25762
R3: 1M; R_0402_1005Metric; LCSC C25762
R4, R5: 10k; R_0402_1005Metric; LCSC C25762
R6: 250K; R_0402_1005Metric; LCSC C25762
SW1: TS-1088R-02026; SW-SMD_L3.9-W3.0-P4.45; LCSC Part C455280
SW2: SW-SMD_L3.9-W3.0-P4.45; LCSC C720477
U1: MCP73831/2; SOT-23-5; LCSC C14879
U2: ESP32-C3FH4; PARTREV V1.0; LCSC C2858491
U3: MIC5504; UDFN-4-1EP_1x1mm_P0.65mm_EP0.48x0.48mm; LCSC C3021135
Y1: XTAL_40MHz; Crystal_SMD_2016-4Pin_2.0x1.6mm; LCSC C2929402

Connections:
+3.3V: C6.1, C7.1, C9.1, C10.1, J1.1, J11.1, LED1.4 (VDD), LED2.4 (VDD), R1.1, R4.1, R5.2, U2.2 (VDD3P3), U2.3 (VDD3P3), U2.11 (VDD3P3_RTC), U2.17 (VDD3P3_CPU), U2.31 (VDDA), U2.32 (VDDA), U3.1 (VOUT)
+5V: J4.1, U1.4 (V_{DD})
+BATT: C2.1, C8.1, J24.1, R3.2, U1.3 (V_{BAT}), U3.3 (EN), U3.4 (VIN)
/ADC_BATT: R3.1, R6.1, U2.10 (MTDI)
/BAT_PRG: R2.2, U1.5 (PROG)
/CSB: J8.1, U2.13 (MTDO)
/ESP_EN: R5.1, U2.6 (GPIO2), U2.7 (CHIP_EN)
/GPIO: J21.1, R1.2, SW1.1, U2.4 (XTAL_32K_P)
/GPIO8: J7.1, J14.1, U2.14 (GPIO8)
/GPIO9: J5.1, J12.1, U2.15 (GPIO9)
/LED_IN: LED2.3 (DI), U2.12 (MTCK)
/PICO: J6.1, J13.1, U2.16 (GPIO10)
/PWM: J18.1, U2.5 (XTAL_32K_N)
/SPICS: J15.1, U2.8 (GPIO3)
/STATUS_CHARGER: U1.1 (STAT)
/U0RX: J16.1, U2.27 (U0RXD)
/U0TX: J17.1, U2.28 (U0TXD)
/USB_D+: J10.1, U2.26 (GPIO19)
/USB_D-: J23.1, U2.25 (GPIO18)
/XTAL_N: C4.1, U2.29 (XTAL_N), Y1.1
/XTAL_P: C5.1, U2.30 (XTAL_P), Y1.3
/antena: AE1.1 (FEED), C1.1, C12.1, L1.1
/extRef: J9.1
/lna_in: C3.1, C12.2, L1.2, U2.1 (LNA_IN)
GND: C1.2, C2.2, C3.2, C4.2, C5.2, C6.2, C7.2, C8.2, C9.2, C10.2, I1.1 (conn), J2.1, J22.1, J25.1, J26.1, LED1.2 (GND), LED2.2 (GND), R2.1, R6.2, SW1.2, SW2.1, U1.2 (V_{SS}), U2.33 (GND), U3.2 (GND), Y1.2, Y1.4
unnamed: LED1.3 (DI), LED2.1 (DO)
unnamed: R4.2, SW2.2, U2.9 (MTMS)

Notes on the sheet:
Battery charging
Insert attach pad
NEOPIXELS
MCU - ESP32-C3
Com. connection
GPIO button
Tension regulator
Battery
Ext. IO
Ext. port

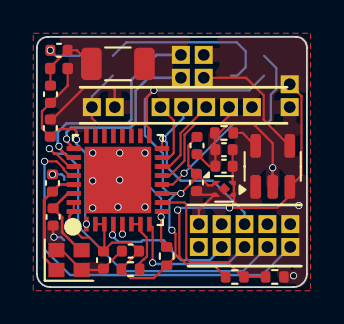
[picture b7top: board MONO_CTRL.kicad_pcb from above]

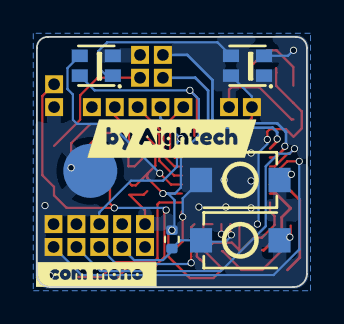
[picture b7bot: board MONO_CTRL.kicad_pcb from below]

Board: 4 copper layers, 15.0 x 13.9 mm, 53 parts (8 on the bottom side), 25 nets.

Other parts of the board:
kibuzzard-66D6133A: G***; kibuzzard-66D6133A
kibuzzard-658C2757: G***; kibuzzard-658C2757

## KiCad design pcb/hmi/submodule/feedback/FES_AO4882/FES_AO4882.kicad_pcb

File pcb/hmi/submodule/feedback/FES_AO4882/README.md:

# FES AO4882 Module
This module is a electrical stimulation module that embeds 2 AO4882 MOSFETs. It is responsible for generating the electrical stimulation signals that will be sent to the electrodes. 

## Electrical Schematic

## PCB Layout
|top view|side view|
|---|---|
 |  |  |

## 3D Model
[FES_AO4882_3D](plots/FES_AO4882_pcb.stl)

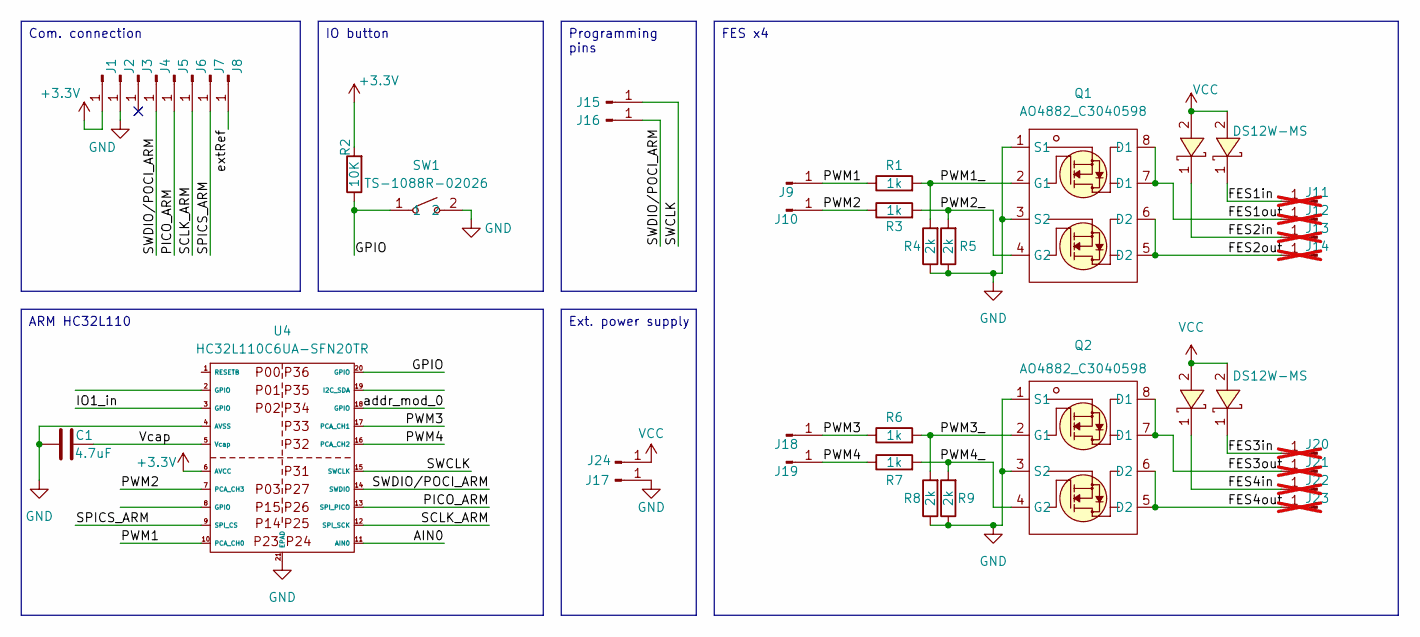
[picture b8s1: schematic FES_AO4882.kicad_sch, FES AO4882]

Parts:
C1: 4.7uF; C_0402_1005Metric; LCSC C23733
J1, J2, J3, J4, J5, J6, J7, J8, J15, J16, J17, J24: Conn_01x01_Pin; PinHeader_1x01_P1.27mm_Vertical
J9, J10, J18, J19: Conn_01x01_Pin; TestPoint_Pad_D1.0mm
J11, J12, J13, J14, J20, J21, J22, J23: Conn_01x01_Pin; PinHeader_1x01_P1.27mm_Vertical; not fitted
Q1, Q2: AO4882_C3040598; SOIC-8_L4.9-W3.9-P1.27-LS6.0-BL; LCSC Part C3040598
R1, R3, R6, R7: 1k; R_0402_1005Metric
R2: 10K; R_0402_1005Metric; LCSC C25744
R4, R5, R8, R9: 2k; R_0402_1005Metric
SW1: TS-1088R-02026; SW-SMD_L3.9-W3.0-P4.45; LCSC Part C455280
U1, U2, U3, U5: DS12W-MS; SOD-123FL_L2.7-W1.8-LS3.8-RD; LCSC Part C5120757
U4: HC32L110C6UA-SFN20TR; WQFN-20_L3.0-W3.0-P0.40-BL-EP; LCSC Part C493490

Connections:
+3.3V: J1.1, R2.2, U4.6 (AVCC)
/AIN0: U4.11 (AIN0)
/FES1in: J11.1, U3.1 (C)
/FES1out: J12.1, Q1.7 (D1), Q1.8 (D1)
/FES2in: J13.1, U2.1 (C)
/FES2out: J14.1, Q1.5 (D2), Q1.6 (D2)
/FES3in: J20.1, U5.1 (C)
/FES3out: J21.1, Q2.7 (D1), Q2.8 (D1)
/FES4in: J22.1, U1.1 (C)
/FES4out: J23.1, Q2.5 (D2), Q2.6 (D2)
/GPIO: R2.1, SW1.1, U4.20 (GPIO)
/IO1_in: U4.3 (GPIO)
/PICO_ARM: J5.1, U4.13 (SPI_PICO)
/PWM1: J9.1, R1.1, U4.10 (PCA_CH0)
/PWM1_: Q1.2 (G1), R1.2, R4.2
/PWM2: J10.1, R3.1, U4.7 (PCA_CH3)
/PWM2_: Q1.4 (G2), R3.2, R5.2
/PWM3: J18.1, R6.1, U4.17 (PCA_CH1)
/PWM3_: Q2.2 (G1), R6.2, R8.2
/PWM4: J19.1, R7.1, U4.16 (PCA_CH2)
/PWM4_: Q2.4 (G2), R7.2, R9.2
/SCLK_ARM: J6.1, U4.12 (SPI_SCK)
/SPICS_ARM: J7.1, U4.9 (SPI_CS)
/SWCLK: J15.1, U4.15 (SWCLK)
/SWDIO/POCI_ARM: J4.1, J16.1, U4.14 (SWDIO)
/Vcap: C1.2, U4.5 (Vcap)
/addr_mod_0: U4.18 (GPIO)
/extRef: J8.1
GND: C1.1, J2.1, J17.1, Q1.1 (S1), Q1.3 (S2), Q2.1 (S1), Q2.3 (S2), R4.1, R5.1, R8.1, R9.1, SW1.2, U4.4 (AVSS), U4.21 (EPAD)
VCC: J24.1, U1.2 (A), U2.2 (A), U3.2 (A), U5.2 (A)

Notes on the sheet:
ARM HC32L110
Com. connection
FES x4
IO button
Programming pins
Ext. power supply
